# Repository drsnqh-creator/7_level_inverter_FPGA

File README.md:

# 7_level_inverter_FPGA
7 level, Ma 0.96, Dead-time 300ns, Fs ~25.6khz

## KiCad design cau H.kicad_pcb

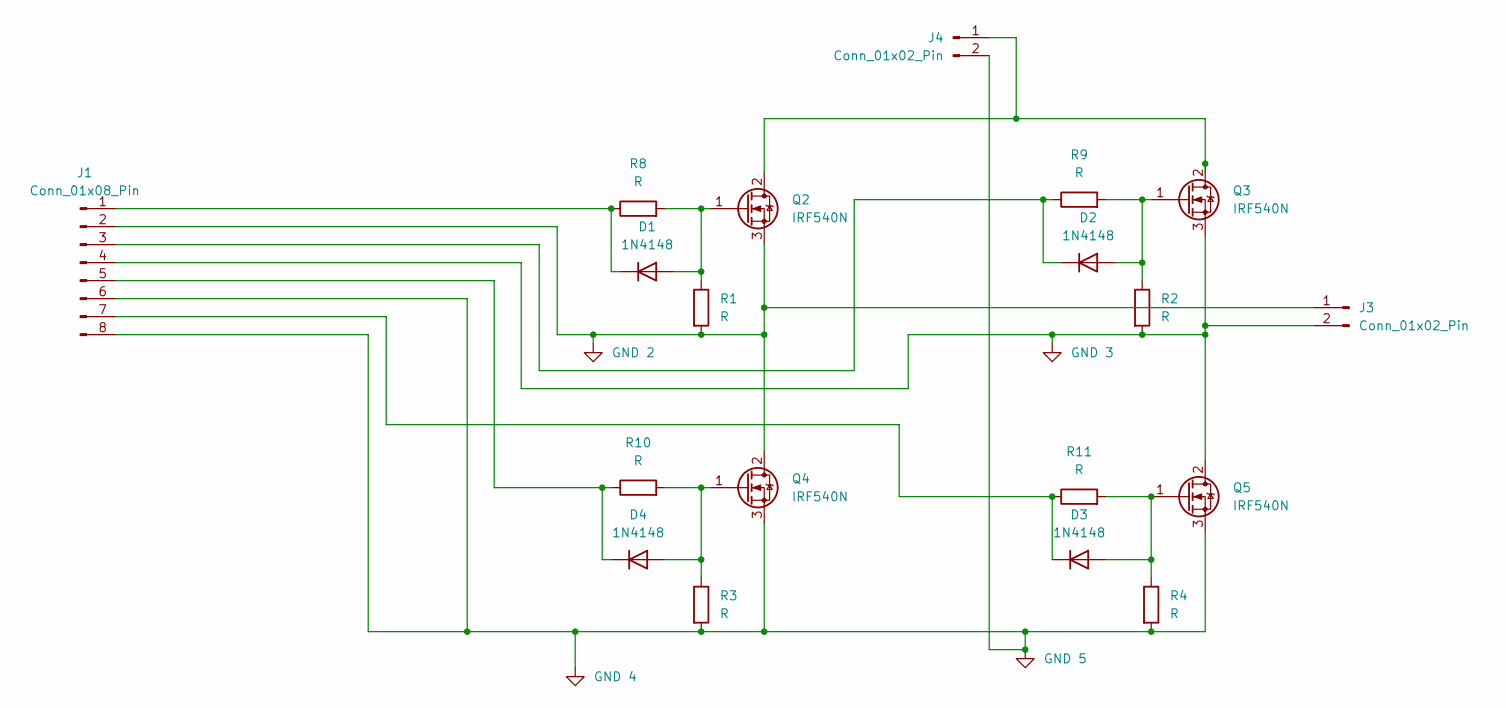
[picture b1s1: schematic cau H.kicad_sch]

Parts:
D1, D2, D3, D4: 1N4148; D_DO-35_SOD27_P7.62mm_Horizontal
J1: Conn_01x08_Pin; PinHeader_1x08_P2.54mm_Vertical
J3, J4: Conn_01x02_Pin; TerminalBlock_MetzConnect_Type101_RT01602HBWC_1x02_P5.08mm_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
Q2, Q3, Q4, Q5: IRF540N; TO-220-3_Vertical
R1, R2, R3, R4, R8, R9, R10, R11: R; R_Axial_DIN0207_L6.3mm_D2.5mm_P7.62mm_Horizontal

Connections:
GND 2: J1.2, J3.1, Q2.3 (S), Q4.2 (D), R1.2
GND 3: J1.4, J3.2, Q3.3 (S), Q5.2 (D), R2.2
GND 4: J1.6, J1.8, J4.2, Q4.3 (S), Q5.3 (S), R3.2, R4.2
unnamed: D1.2 (A), Q2.1 (G), R1.1, R8.2
unnamed: D1.1 (K), J1.1, R8.1
unnamed: D2.2 (A), Q3.1 (G), R2.1, R9.2
unnamed: D2.1 (K), J1.3, R9.1
unnamed: D3.2 (A), Q5.1 (G), R4.1, R11.2
unnamed: D3.1 (K), J1.7, R11.1
unnamed: D4.2 (A), Q4.1 (G), R3.1, R10.2
unnamed: D4.1 (K), J1.5, R10.1
unnamed: J4.1, Q2.2 (D), Q3.2 (D)

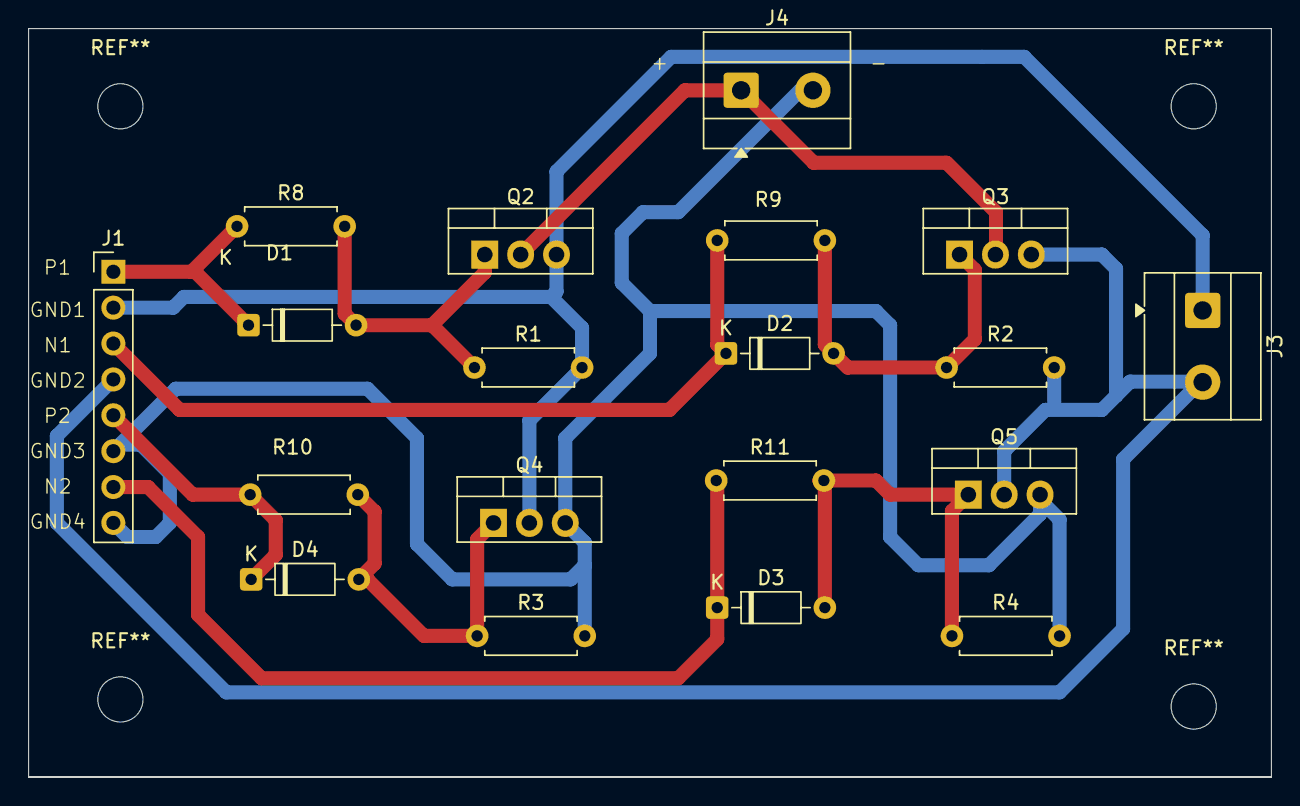
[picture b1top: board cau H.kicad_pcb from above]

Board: 2 copper layers, 88.0 x 53.0 mm, 19 parts (0 on the bottom side), 12 nets.
